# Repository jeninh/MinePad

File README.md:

# MinePad

MinePad is a HackPad for Minecraft lovers, like myself!    
These 9 keys (and rotary dial) are all you need to play Minecraft!    (except for, well... a mouse. one day i can make this into a mouse?!!!)    
Keybinds:   
| Tab | W | E |
|--------|--------|--------| 
| A | S | D |
| F   | Space | Q |

Rotary Encoder:    
Rotating: Scroll Wheel (Clockwise to scroll down, Counter-Clockwise to scroll up)   
Click: CTRL   

# CAD Model
Everything is connected by 4 M3 Screws. It contains two pieces, the base and the lid. Made in Fusion360, which probably took me 10 hours to learn. I'm pretty good at it now!!!   

# PCB
PCB was made in KiCad, thanks to Meghana for helping me make it in her seminar.   

# Firmware
I used KMK for the firmware, you can find it inside the firmware folder. Was coded in Python!!!   

# BOM
- Seeed XIAO RP2040
- 9x MX-Style Switches
- 1x EC11 Rotary Encoder
- 9x Blank DSA Keycaps (I'm going to paint em!)
- 3d Printed Case

# Extra Stuff
I like trains! And Minecraft!

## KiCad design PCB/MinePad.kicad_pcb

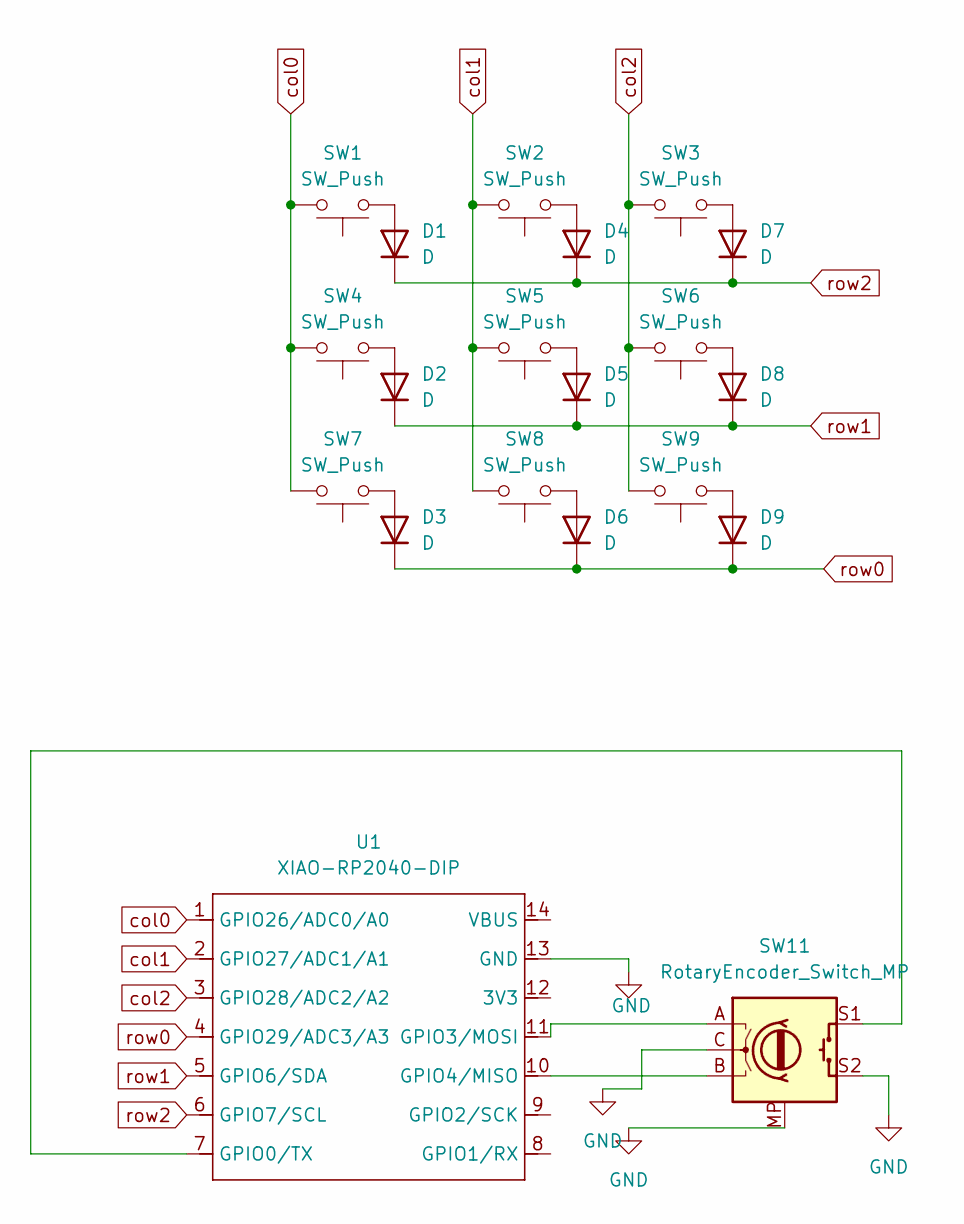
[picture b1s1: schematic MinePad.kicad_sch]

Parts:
D1, D2, D3, D4, D5, D6, D7, D8, D9: D; D_DO-35_SOD27_P2.54mm_Vertical_AnodeUp
SW1, SW2, SW3, SW4, SW5, SW6, SW7, SW8, SW9: SW_Push; SW_Cherry_MX_1.00u_PCB
SW11: RotaryEncoder_Switch_MP; RotaryEncoder_Alps_EC11E-Switch_Vertical_H20mm_CircularMoun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
U1: XIAO-RP2040-DIP

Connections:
GND: SW11.C, SW11.MP, SW11.S2, U1.13 (GND)
unnamed: D1.2 (A), SW1.1
unnamed: D2.2 (A), SW4.1
unnamed: D3.2 (A), SW7.1
unnamed: D4.2 (A), SW2.1
unnamed: D5.2 (A), SW5.1
unnamed: D6.2 (A), SW8.1
unnamed: D7.2 (A), SW3.1
unnamed: D8.2 (A), SW6.1
unnamed: D9.2 (A), SW9.1
unnamed: SW11.S1, U1.7 (GPIO0/TX)
unnamed: SW11.A, U1.11 (GPIO3/MOSI)
unnamed: SW11.B, U1.10 (GPIO4/MISO)
col0: SW1.2, SW4.2, SW7.2, U1.1 (GPIO26/ADC0/A0)
col1: SW2.2, SW5.2, SW8.2, U1.2 (GPIO27/ADC1/A1)
col2: SW3.2, SW6.2, SW9.2, U1.3 (GPIO28/ADC2/A2)
row0: D3.1 (K), D6.1 (K), D9.1 (K), U1.4 (GPIO29/ADC3/A3)
row1: D2.1 (K), D5.1 (K), D8.1 (K), U1.5 (GPIO6/SDA)
row2: D1.1 (K), D4.1 (K), D7.1 (K), U1.6 (GPIO7/SCL)

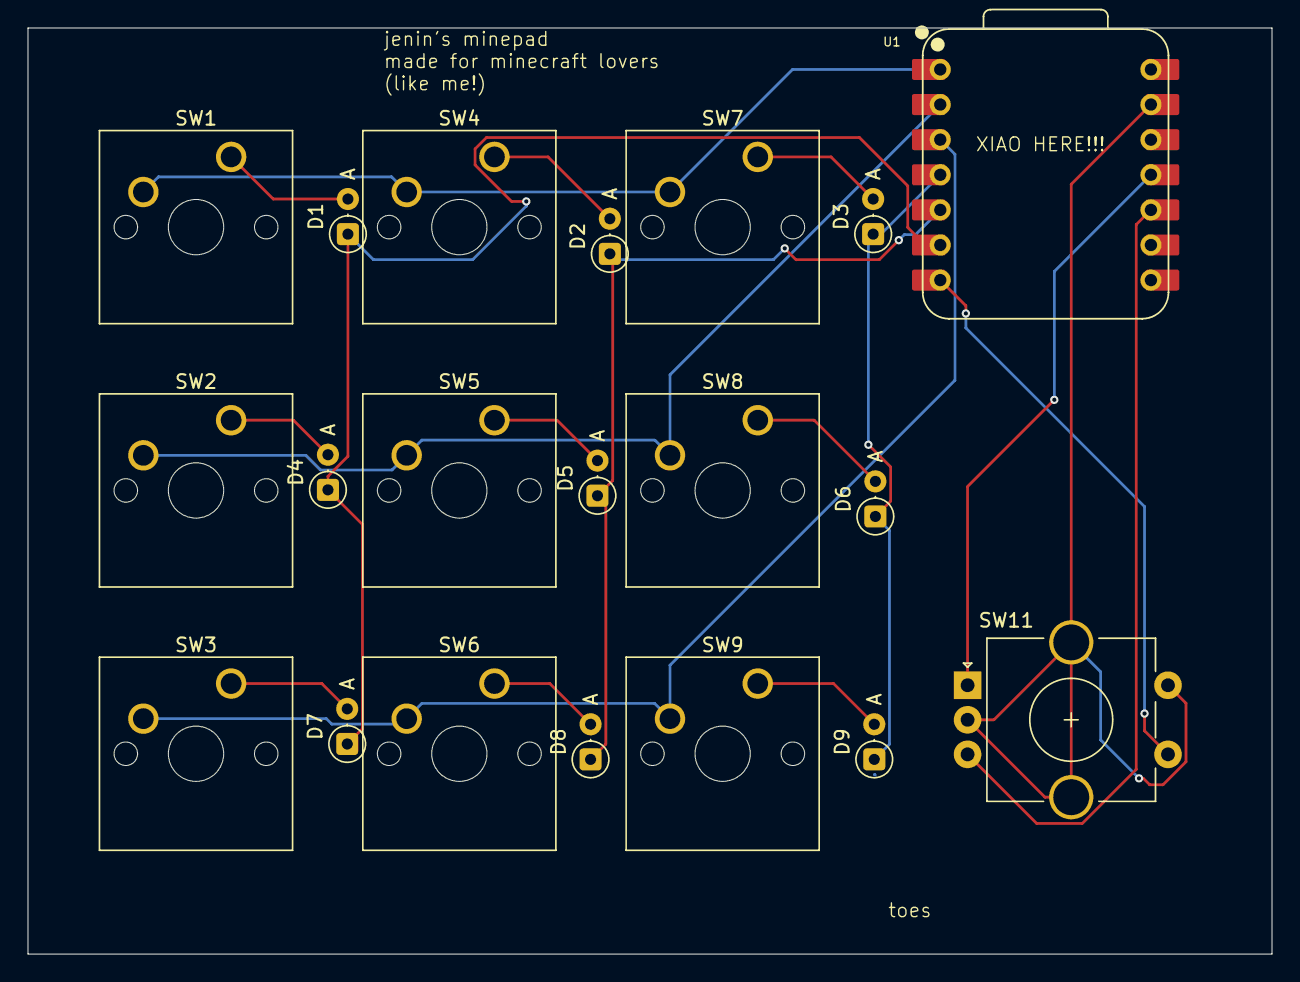
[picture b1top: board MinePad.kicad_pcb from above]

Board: 2 copper layers, 90.0 x 67.0 mm, 20 parts (0 on the bottom side), 19 nets.

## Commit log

2025-06-28 Add Assembled MinePad
2025-06-28 Add MinePad Schematics
2025-06-28 main.pie
2025-07-26 Update main.py
    ty @Overlord-Runt!!
2025-10-30 test commit
